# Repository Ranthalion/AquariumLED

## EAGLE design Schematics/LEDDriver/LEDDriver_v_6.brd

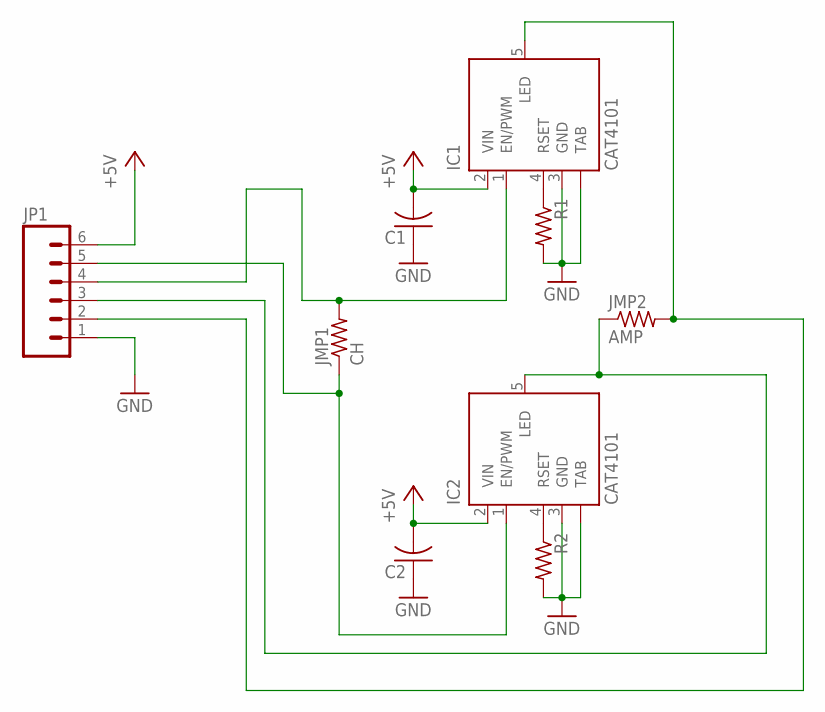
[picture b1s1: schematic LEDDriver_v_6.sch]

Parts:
C1, C2: C-USC1206; C1206
IC1, IC2: CAT4101; TO263_5
JMP1: CH; R1206
JMP2: AMP; R1206
JP1: M06LOCK_LONGPADS; 1X06_LOCK_LONGPADS
R1, R2: R-US_R1206; R1206

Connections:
+5V: C1.2, C2.2, IC1.2 (VIN), IC2.2 (VIN), JP1.6
GND: C1.1, C2.1, IC1.3 (GND), IC1.TAB, IC2.3 (GND), IC2.TAB, JP1.1, R1.2, R2.2
unnamed: IC1.1 (EN/PWM), JMP1.2, JP1.4
unnamed: IC2.1 (EN/PWM), JMP1.1, JP1.5
unnamed: IC1.4 (RSET), R1.1
unnamed: IC2.5 (LED), JMP2.1, JP1.3
unnamed: IC1.5 (LED), JMP2.2, JP1.2
unnamed: IC2.4 (RSET), R2.1

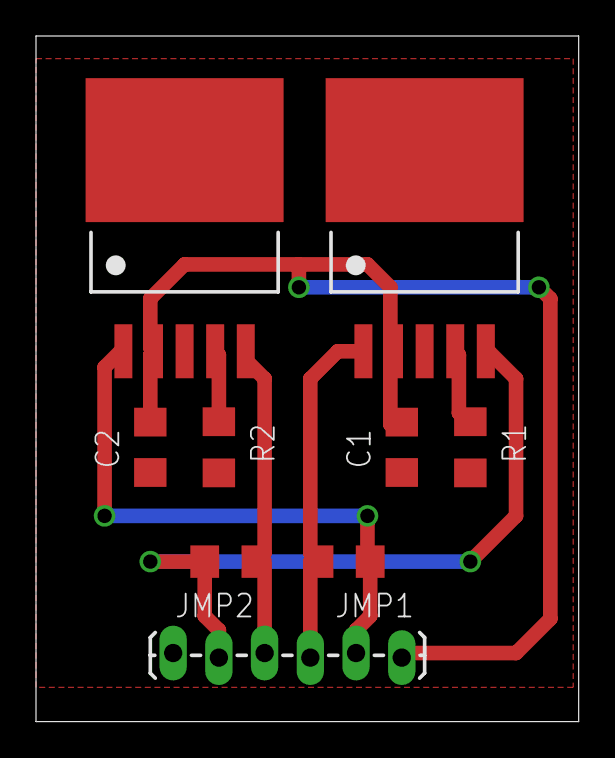
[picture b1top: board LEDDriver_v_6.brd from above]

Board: 2 copper layers, 30.1 x 38.1 mm, 9 parts (0 on the bottom side), 8 nets.

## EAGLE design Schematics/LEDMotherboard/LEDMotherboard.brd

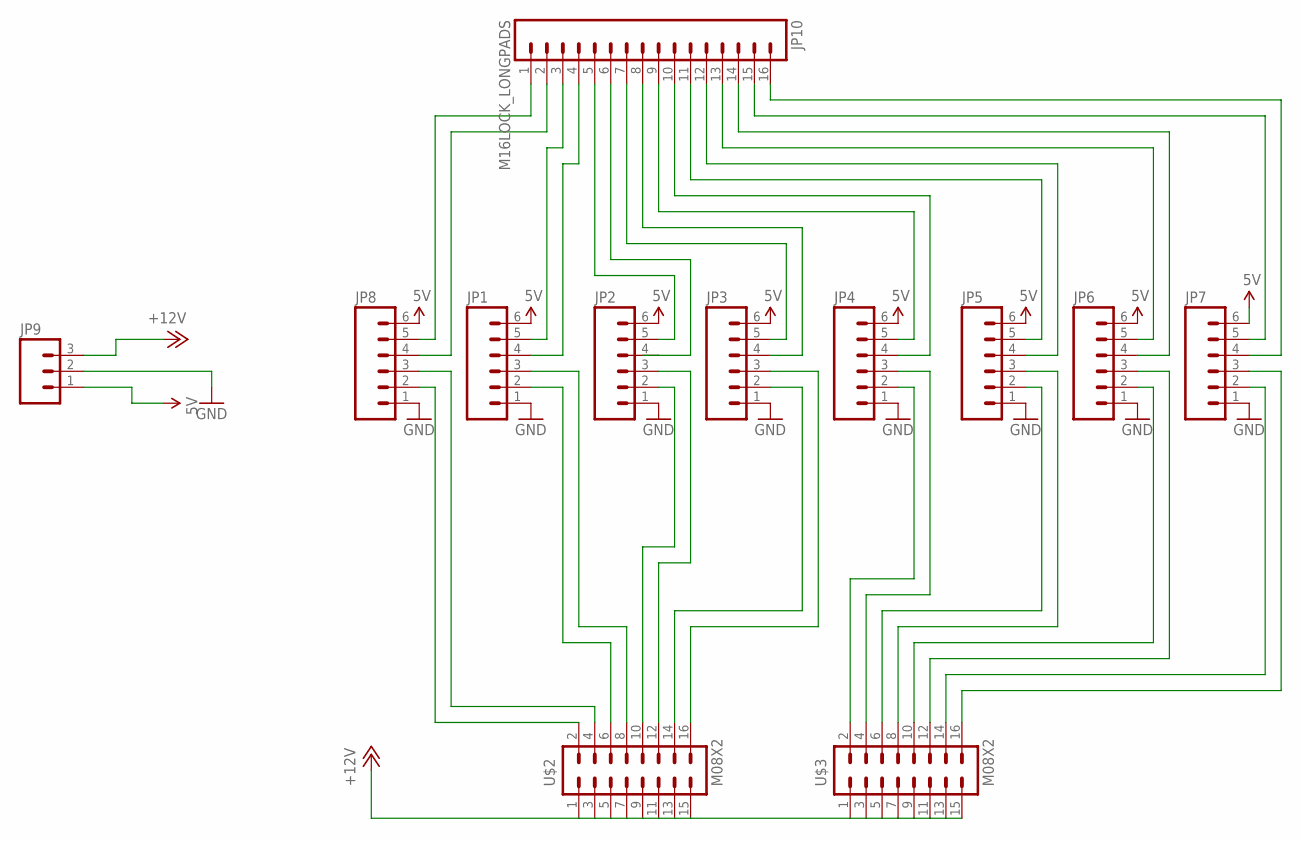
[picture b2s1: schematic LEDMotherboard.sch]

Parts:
JP1, JP2, JP3, JP4, JP5, JP6, JP7, JP8: M06LOCK_LONGPADS; 1X06_LOCK_LONGPADS
JP9: M03-SCREW-5MM; SCREWTERMINAL-5MM-3
JP10: M16LOCK_LONGPADS; 1X16_LOCK_LONGPADS
U$2, U$3: M08X2; 2X8

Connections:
5V: JP1.6, JP2.6, JP3.6, JP4.6, JP5.6, JP6.6, JP7.6, JP8.6, JP9.1
+12V: JP9.3, U$2.1, U$2.3, U$2.5, U$2.7, U$2.9, U$2.11, U$2.13, U$2.15, U$3.1, U$3.3, U$3.5, U$3.7, U$3.9, U$3.11, U$3.13, U$3.15
GND: JP1.1, JP2.1, JP3.1, JP4.1, JP5.1, JP6.1, JP7.1, JP8.1, JP9.2
unnamed: JP8.4, JP10.2
unnamed: JP8.3, U$2.4
unnamed: JP8.5, JP10.1
unnamed: JP5.4, JP10.12
unnamed: JP1.5, JP10.3
unnamed: JP1.4, JP10.4
unnamed: JP1.2, U$2.6
unnamed: JP1.3, U$2.8
unnamed: JP3.5, JP10.7
unnamed: JP3.4, JP10.8
unnamed: JP4.5, JP10.9
unnamed: JP4.4, JP10.10
unnamed: JP5.5, JP10.11
unnamed: JP6.5, JP10.13
unnamed: JP6.4, JP10.14
unnamed: JP7.5, JP10.15
unnamed: JP7.4, JP10.16
unnamed: JP2.2, U$2.10
unnamed: JP2.3, U$2.12
unnamed: JP3.3, U$2.16
unnamed: JP3.2, U$2.14
unnamed: JP4.2, U$3.2
unnamed: JP8.2, U$2.2
unnamed: JP2.4, JP10.6
unnamed: JP4.3, U$3.4
unnamed: JP5.2, U$3.6
unnamed: JP5.3, U$3.8
unnamed: JP6.2, U$3.10
unnamed: JP6.3, U$3.12
unnamed: JP7.2, U$3.14
unnamed: JP7.3, U$3.16
unnamed: JP2.5, JP10.5

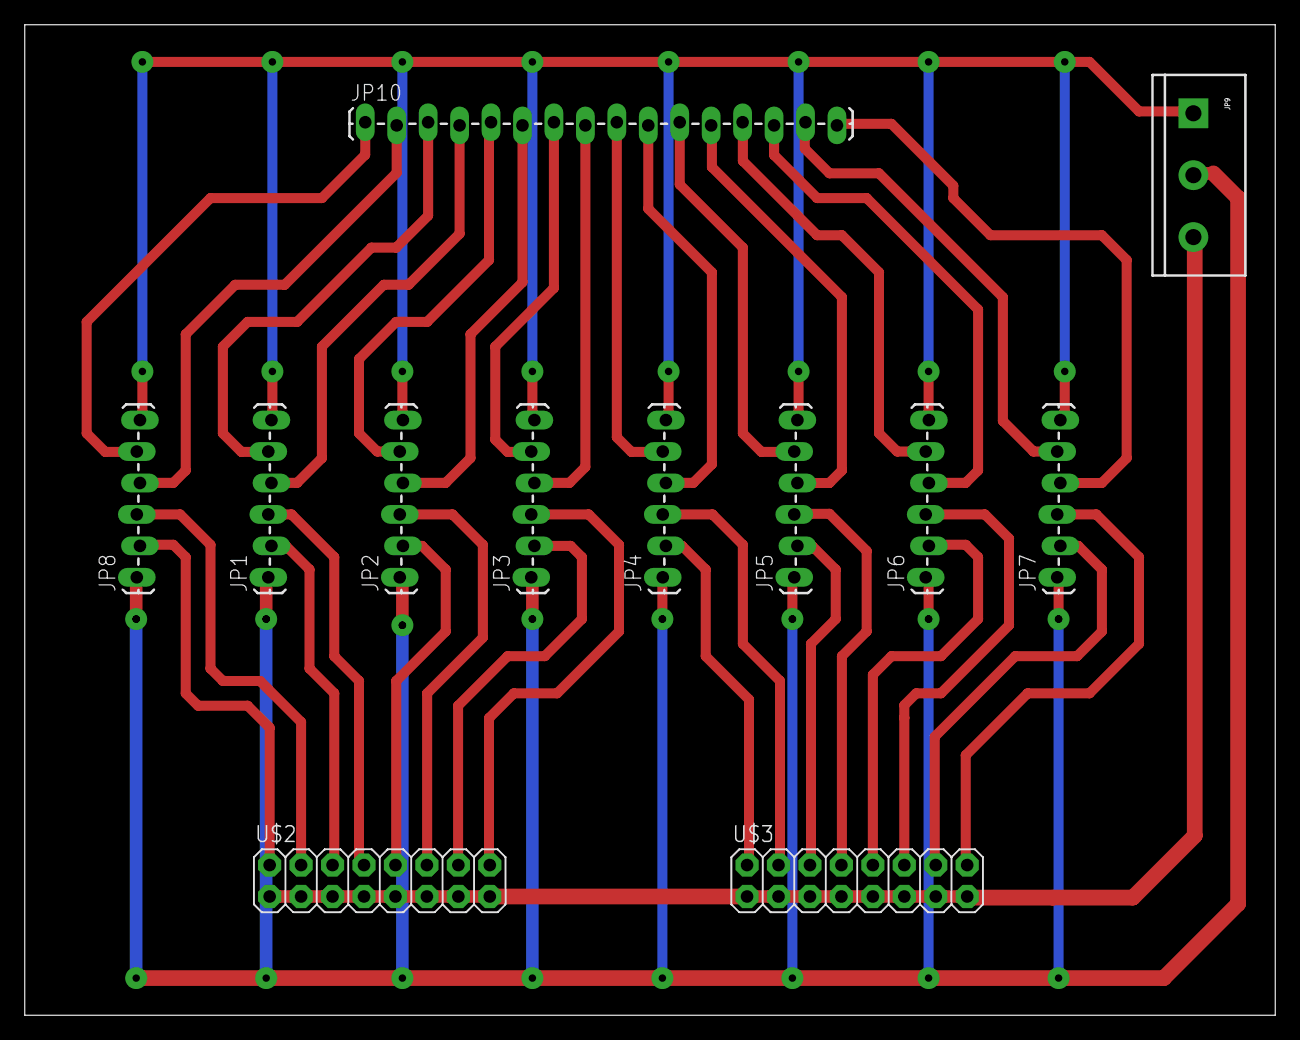
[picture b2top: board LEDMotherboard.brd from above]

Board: 2 copper layers, 101.0 x 80.0 mm, 12 parts (0 on the bottom side), 35 nets.

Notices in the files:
parts and their libraries:
SparkFun-Connectors: Licensing: CC v3.0 Share-Alike You are welcome to use this library for commercial purposes.
